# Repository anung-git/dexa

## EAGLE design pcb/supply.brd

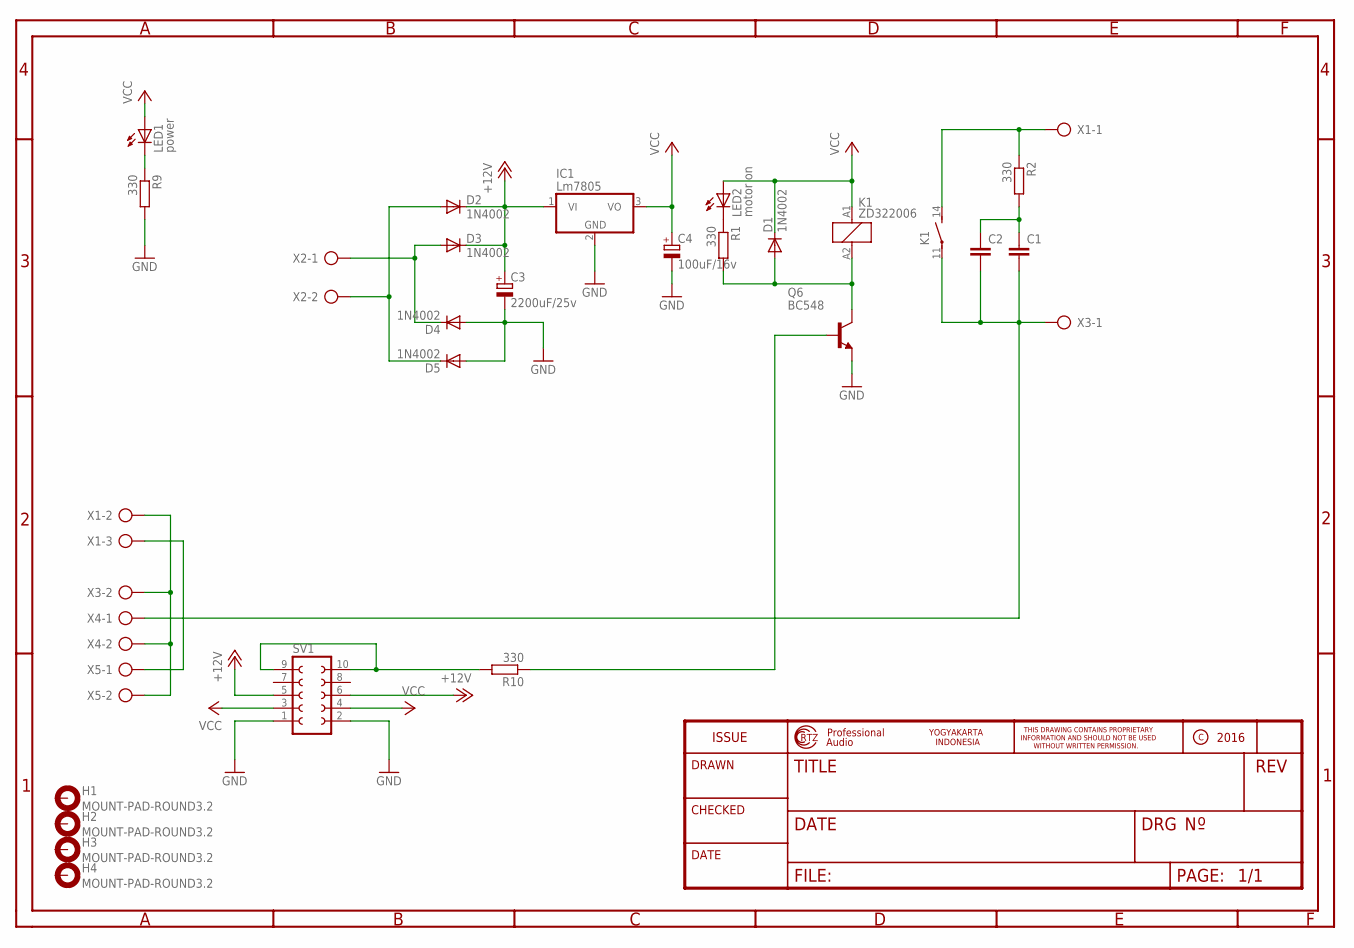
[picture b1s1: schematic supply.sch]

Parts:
C1: C-EU150-084X183; C150-084X183
C2: C-EU102-043X133; C102-043X133
C3: 2200uF/25v; E5-8,5
C4: 100uF/16v; B45181B
D1, D2, D3, D4, D5: 1N4002; DO35-10
H1, H2, H3, H4: MOUNT-PAD-ROUND3.2; 3,2-PAD
IC1: Lm7805; TO220V
K1: ZD322006; ZD2
LED1: power; LED5MM
LED2: motor on; LED5MM
Q6: BC548; TO92-EBC
R1, R2, R9, R10: 330; 0207/7
SV1: FE05-2
X1: AK500/3
X2, X3, X4, X5: AK500/2

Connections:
+12V: C3.+, D2.C, D3.C, IC1.1 (VI), SV1.5, SV1.6
GND: C3.-, C4.-, D4.A, D5.A, IC1.2 (GND), Q6.E, R9.2, SV1.1, SV1.2
GND1: D1.A, K1.A2 (2), Q6.C, R1.2
unnamed: LED2.K (C), R1.1
unnamed: LED1.K (C), R9.1
unnamed: D3.A, D4.C, X2.1
unnamed: D2.A, D5.C, X2.2
unnamed: C1.1, C2.1, R2.2
unnamed: C1.2, C2.2, K1.11, X3.1, X4.1
unnamed: K1.14 (S), R2.1, X1.1
unnamed: X1.2, X3.2, X4.2, X5.2
unnamed: X1.3, X5.1
unnamed: R10.2, SV1.9, SV1.10
unnamed: Q6.B, R10.1
VCC: C4.+, D1.C, IC1.3 (VO), K1.A1 (1), LED1.A, LED2.A, SV1.3, SV1.4

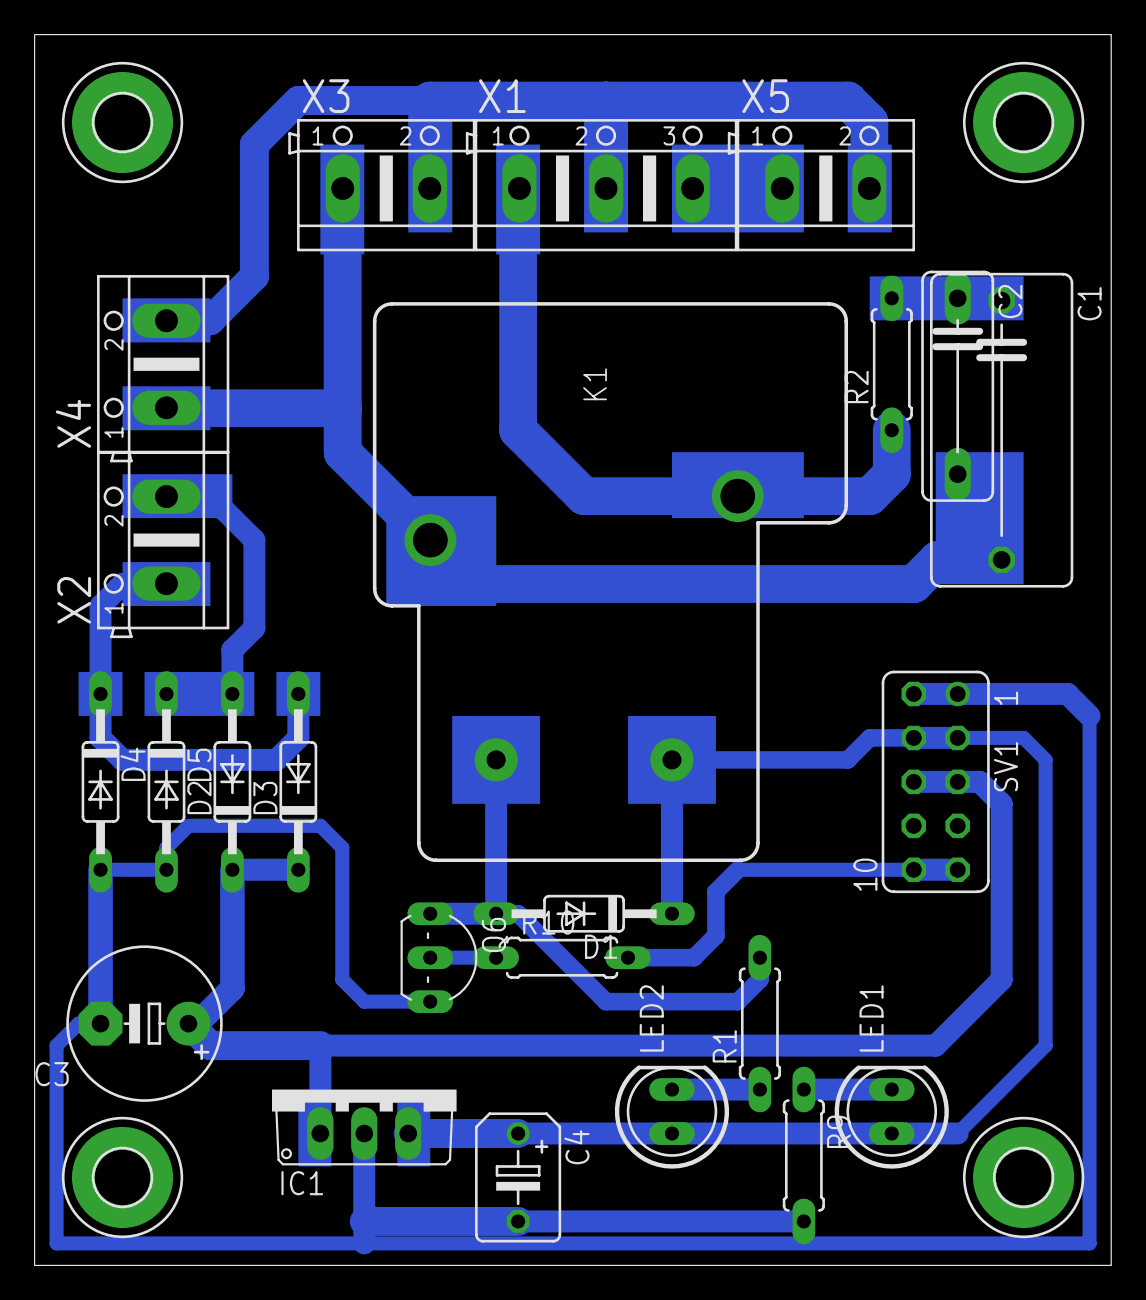
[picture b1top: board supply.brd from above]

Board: 2 copper layers, 62.2 x 71.1 mm, 28 parts (0 on the bottom side), 15 nets.

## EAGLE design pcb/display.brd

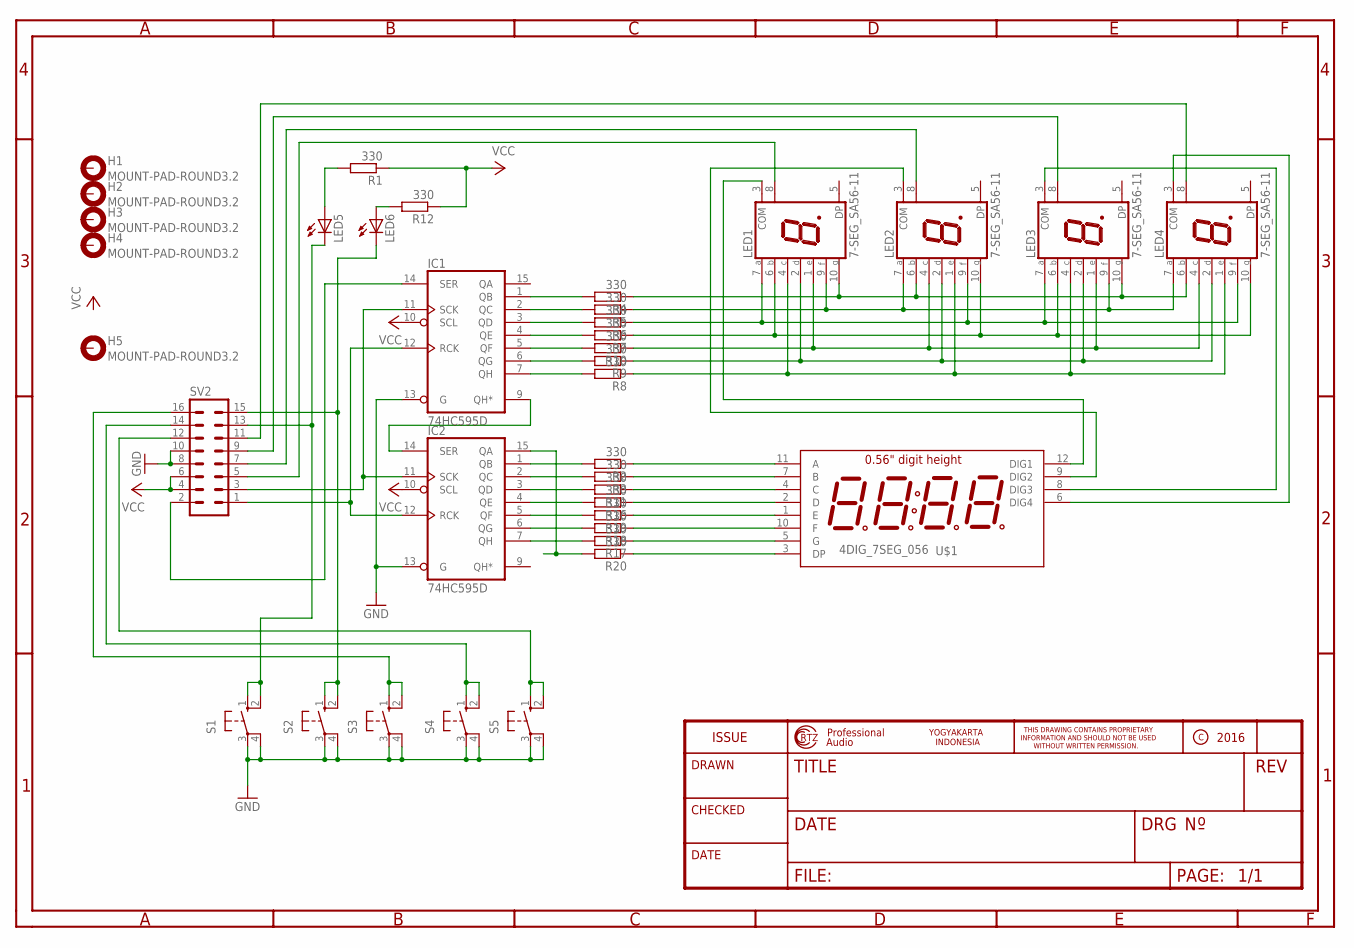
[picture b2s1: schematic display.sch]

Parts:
H1, H2, H3, H4, H5: MOUNT-PAD-ROUND3.2; 3,2-PAD
IC1, IC2: 74HC595D; SO16
LED1, LED2, LED3, LED4: 7-SEG_SA56-11; SA56-11
LED5, LED6: LED5MM
R1, R2, R3, R4, R5, R6, R7, R8, R9, R10, R11, R12, R16, R17, R18, R19, R20: 330; 0207/7
S1, S2, S3, S4, S5: 40-XX; B3F-40XX
SV2: MA08-2W
U$1: 4DIG_7SEG_056

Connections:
GND: IC1.8 (GND), IC1.13 (G), IC2.8 (GND), IC2.13 (G), S1.3, S1.4 (P1), S2.3, S2.4 (P1), S3.3, S3.4 (P1), S4.3, S4.4 (P1), S5.3, S5.4 (P1), SV2.8, SV2.10
unnamed: IC1.2 (QC), R5.2
unnamed: LED1.7 (A), LED2.9 (F), LED3.7 (A), LED4.9 (F), R6.1
unnamed: LED1.1 (E), LED2.4 (C), LED3.1 (E), LED4.4 (C), R10.1
unnamed: LED1.2 (D), LED2.2 (D), LED3.2 (D), LED4.2 (D), R9.1
unnamed: LED1.6 (B), LED2.10 (G), LED3.6 (B), LED4.10 (G), R7.1
unnamed: LED1.3 (COM), U$1.12 (DIG1)
unnamed: LED2.3 (COM), U$1.9 (DIG2)
unnamed: LED1.4 (C), LED2.1 (E), LED3.4 (C), LED4.1 (E), R8.1
unnamed: IC2.2 (QC), R3.2
unnamed: IC2.3 (QD), R11.2
unnamed: IC1.11 (SCK), IC2.11 (SCK), SV2.3
unnamed: IC1.3 (QD), R6.2
unnamed: IC1.12 (RCK), IC2.12 (RCK), SV2.1
unnamed: LED3.3 (COM), U$1.8 (DIG3)
unnamed: LED4.3 (COM), U$1.6 (DIG4)
unnamed: IC1.4 (QE), R7.2
unnamed: IC1.5 (QF), R10.2
unnamed: IC1.6 (QG), R9.2
unnamed: IC1.7 (QH), R8.2
unnamed: IC1.1 (QB), R4.2
unnamed: IC1.14 (SER), SV2.2
unnamed: IC2.4 (QE), R16.2
unnamed: IC2.6 (QG), R18.2
unnamed: LED4.8 (COM), SV2.11
unnamed: LED2.8 (COM), SV2.7
unnamed: LED3.8 (COM), SV2.9
unnamed: LED1.10 (G), LED2.6 (B), LED3.10 (G), LED4.6 (B), R4.1
unnamed: LED1.8 (COM), SV2.5
unnamed: LED5.A, R1.2
unnamed: LED6.A, R12.2
unnamed: IC2.5 (QF), R19.2
unnamed: LED1.9 (F), LED2.7 (A), LED3.9 (F), LED4.7 (A), R5.1
unnamed: IC2.7 (QH), R17.2
unnamed: IC2.1 (QB), R2.2
unnamed: R2.1, U$1.11 (A)
unnamed: R3.1, U$1.7 (B)
unnamed: R11.1, U$1.4 (C)
unnamed: R16.1, U$1.2 (D)
unnamed: R17.1, U$1.5 (G)
unnamed: R18.1, U$1.10 (F)
unnamed: R19.1, U$1.1 (E)
unnamed: R20.1, U$1.3 (DP)
unnamed: IC2.15 (QA), R20.2
unnamed: LED5.K (C), S1.1 (S), S1.2 (S1), SV2.13
unnamed: LED6.K (C), S2.1 (S), S2.2 (S1), SV2.15
unnamed: S3.1 (S), S3.2 (S1), SV2.16
unnamed: S4.1 (S), S4.2 (S1), SV2.14
unnamed: S5.1 (S), S5.2 (S1), SV2.12
unnamed: IC1.9 (QH*), IC2.14 (SER)
VCC: IC1.10 (SCL), IC1.16 (VCC), IC2.10 (SCL), IC2.16 (VCC), R1.1, R12.1, SV2.4, SV2.6

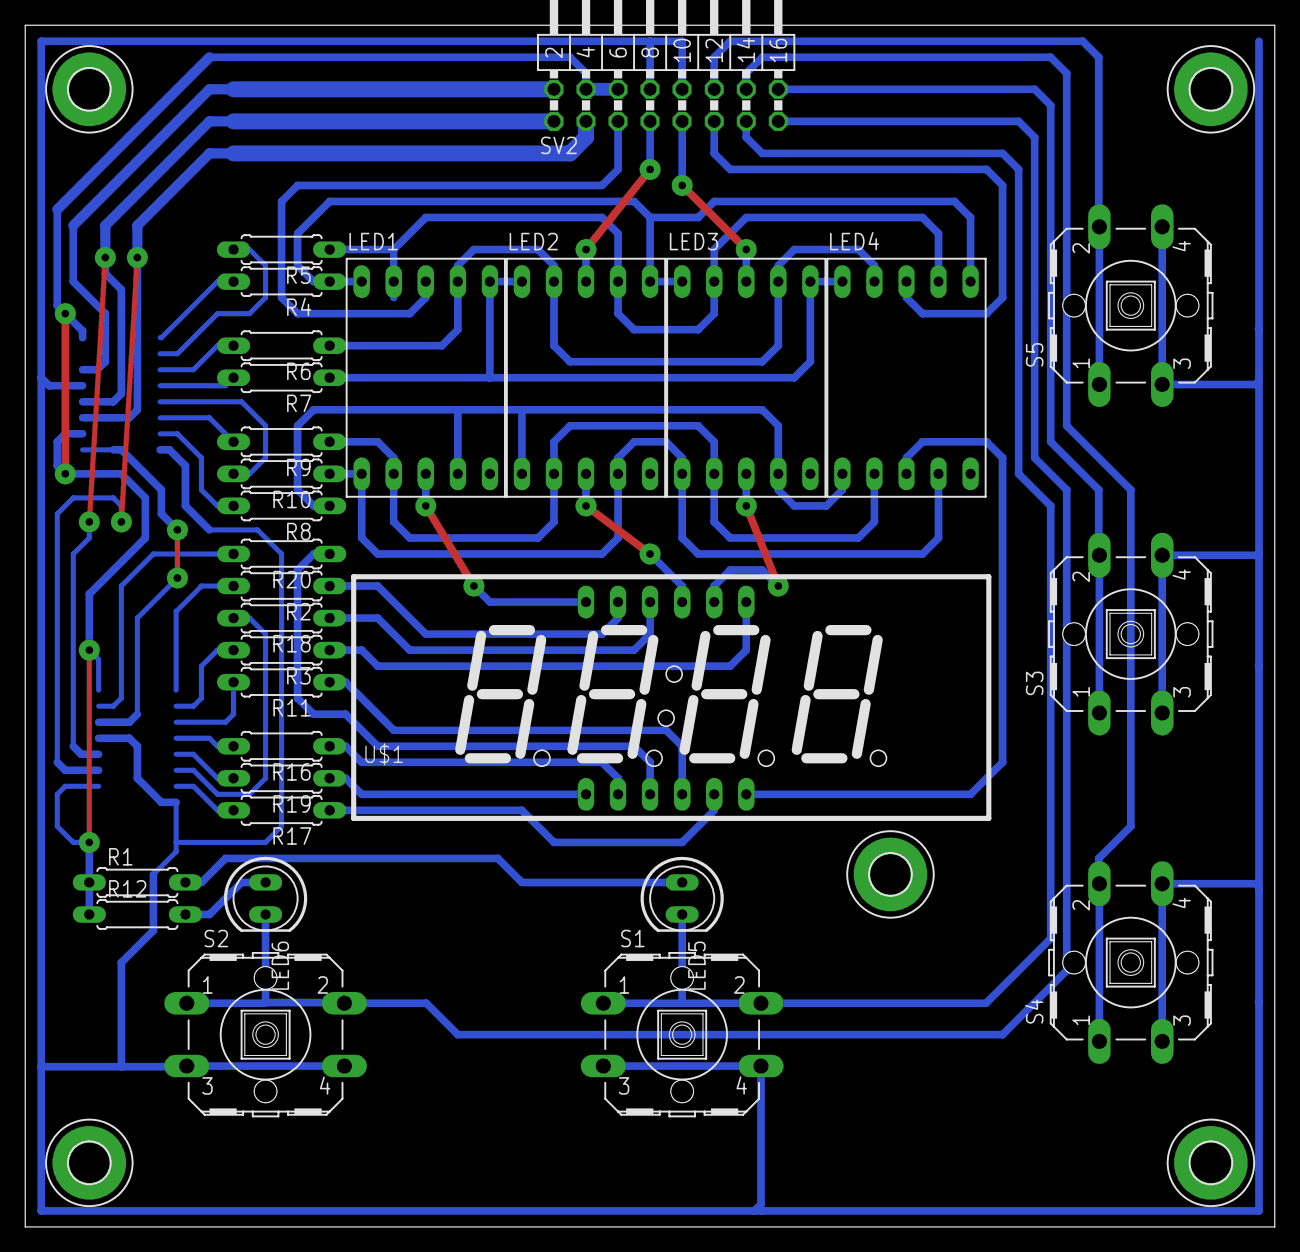
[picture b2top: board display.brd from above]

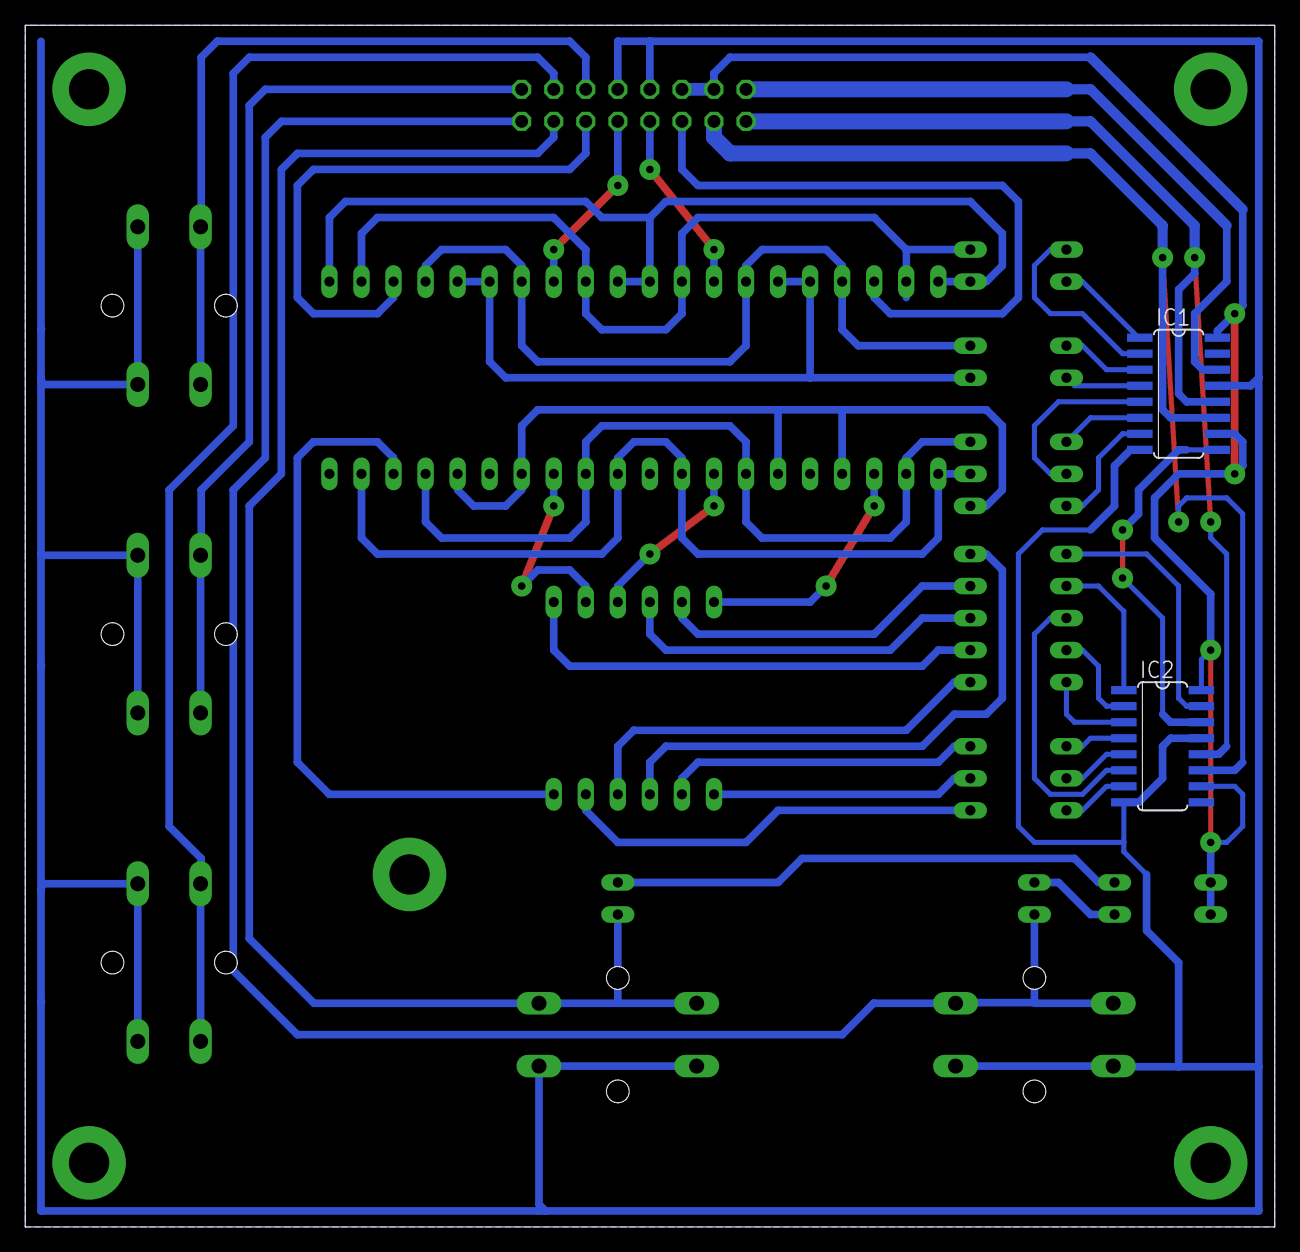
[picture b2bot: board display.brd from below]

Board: 2 copper layers, 99.0 x 95.2 mm, 37 parts (2 on the bottom side), 51 nets.

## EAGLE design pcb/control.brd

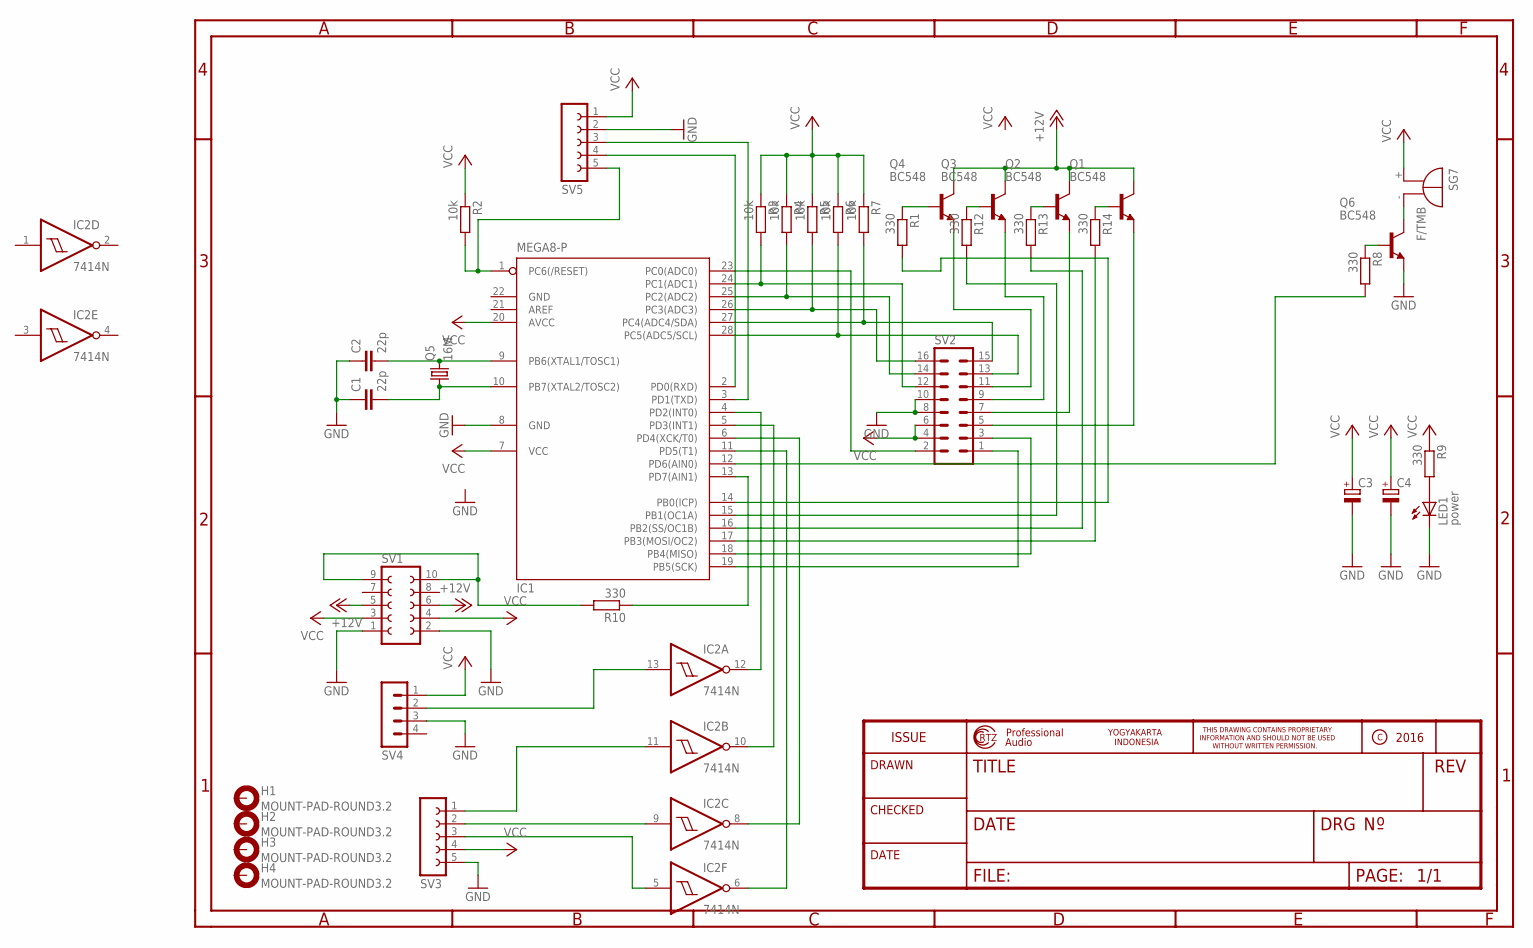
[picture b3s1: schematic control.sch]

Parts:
C1, C2: 22p; C025-025X050
C3, C4: CPOL-EUB45181B; B45181B
H1, H2, H3, H4: MOUNT-PAD-ROUND3.2; 3,2-PAD
IC1: MEGA8-P; DIL28-3
IC2: 7414N; DIL14
LED1: power; LED5MM
Q1, Q2, Q3, Q4, Q6: BC548; TO92-EBC
Q5: 16M; HC49U-V
R1, R8, R9, R10, R12, R13, R14: 330; 0207/7
R2, R3, R4, R5, R6, R7: 10k; 0207/7
SG7: F/TMB
SV1: FE05-2
SV2: MA08-2
SV3, SV5: FE05-1
SV4: MA04-1

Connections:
+12V: Q1.C, Q2.C, Q3.C, Q4.C, SV1.5, SV1.6
GND: C1.1, C2.1, C3.-, C4.-, IC1.8 (GND), IC1.22 (GND), IC2.7 (GND), LED1.K (C), Q6.E, SV1.1, SV1.2, SV2.8, SV2.10, SV3.5, SV4.3, SV5.2
unnamed: IC1.1 (PC6(/RESET)), R2.2, SV5.5
unnamed: C1.2, IC1.10 (PB7(XTAL2/TOSC2)), Q5.1
unnamed: C2.2, IC1.9 (PB6(XTAL1/TOSC1)), Q5.2
unnamed: IC1.24 (PC1(ADC1)), R3.2, SV2.12
unnamed: IC1.23 (PC0(ADC0)), SV2.2
unnamed: IC1.15 (PB1(OC1A)), R12.2
unnamed: IC1.16 (PB2(SS/OC1B)), R13.2
unnamed: IC1.17 (PB3(MOSI/OC2)), R14.2
unnamed: IC1.28 (PC5(ADC5/SCL)), R6.2, SV2.13
unnamed: Q4.B, R1.1
unnamed: Q6.C, SG7.-
unnamed: Q6.B, R8.1
unnamed: LED1.A, R9.2
unnamed: R10.2, SV1.9, SV1.10
unnamed: IC1.4 (PD2(INT0)), IC2.12 (O)
unnamed: IC1.13 (PD7(AIN1)), R10.1
unnamed: IC1.5 (PD3(INT1)), IC2.10 (O)
unnamed: Q3.B, R12.1
unnamed: IC1.6 (PD4(XCK/T0)), IC2.8 (O)
unnamed: IC1.12 (PD6(AIN0)), R8.2
unnamed: Q4.E, SV2.11
unnamed: Q2.E, SV2.7
unnamed: Q3.E, SV2.9
unnamed: IC2.13 (I), SV4.2
unnamed: Q1.E, SV2.5
unnamed: Q2.B, R13.1
unnamed: Q1.B, R14.1
unnamed: IC2.11 (I), SV3.1
unnamed: IC2.9 (I), SV3.2
unnamed: IC2.5 (I), SV3.3
unnamed: IC1.11 (PD5(T1)), IC2.6 (O)
unnamed: IC1.27 (PC4(ADC4/SDA)), R7.2, SV2.15
unnamed: IC1.2 (PD0(RXD)), SV5.4
unnamed: IC1.3 (PD1(TXD)), SV5.3
unnamed: IC1.14 (PB0(ICP)), R1.2
unnamed: IC1.19 (PB5(SCK)), SV2.1
unnamed: IC1.18 (PB4(MISO)), SV2.3
unnamed: IC1.25 (PC2(ADC2)), R4.2, SV2.14
unnamed: IC1.26 (PC3(ADC3)), R5.2, SV2.16
VCC: C3.+, C4.+, IC1.7 (VCC), IC1.20 (AVCC), IC2.14 (VCC), R2.1, R3.1, R4.1, R5.1, R6.1, R7.1, R9.1, SG7.+, SV1.3, SV1.4, SV2.4, SV2.6, SV3.4, SV4.1, SV5.1

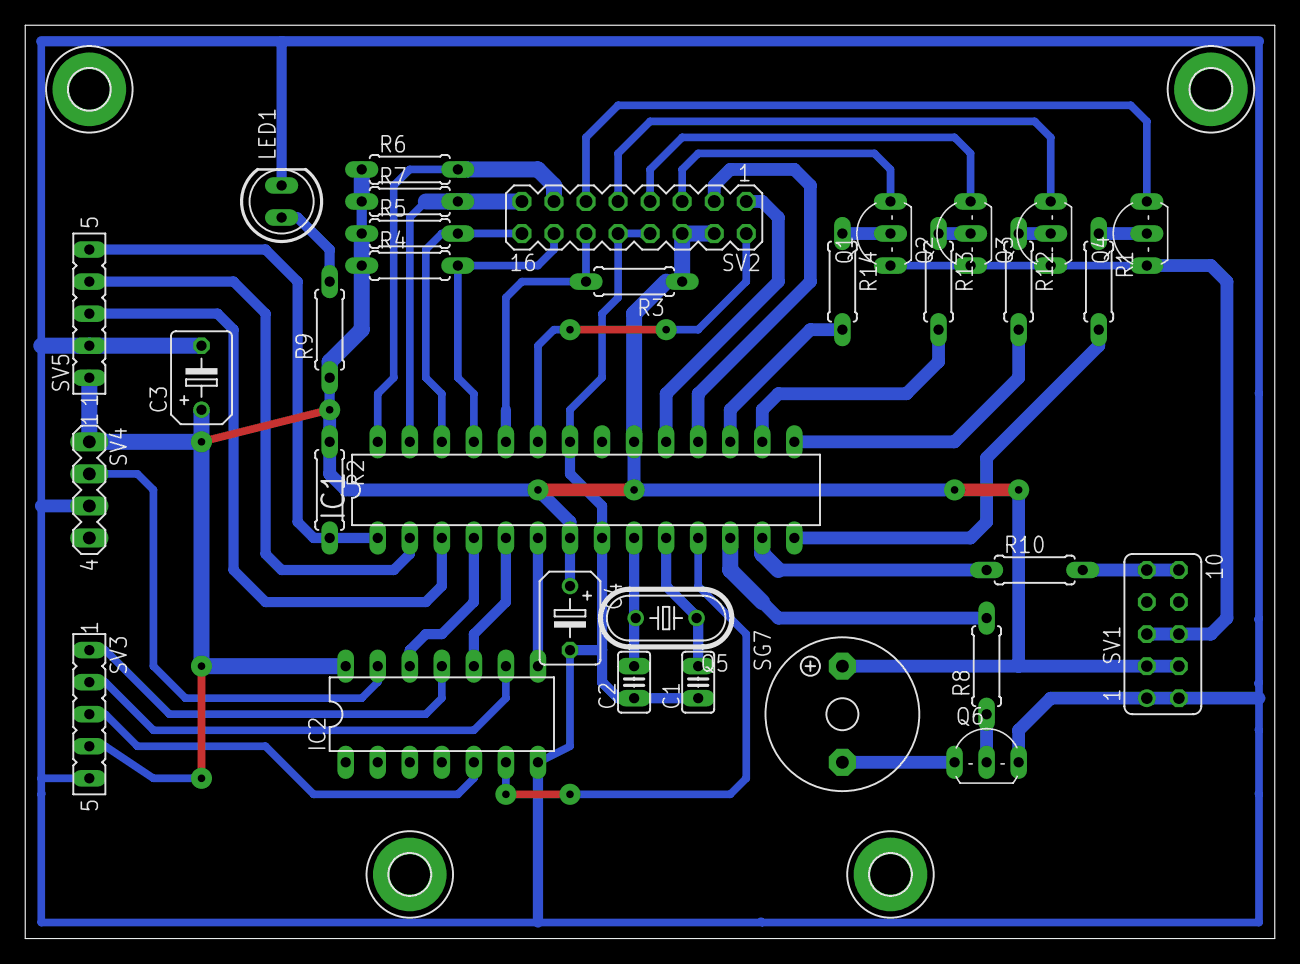
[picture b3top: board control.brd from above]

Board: 2 copper layers, 99.0 x 72.4 mm, 36 parts (0 on the bottom side), 42 nets.

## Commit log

2021-08-27 upload
2021-08-27 interup rpm
2021-08-28 add rpm display
2021-08-29 add class buzer
2021-08-29 disable button
2021-08-29 edit pcb
2021-08-29 ganti pcb
2021-08-30 auto reset
2021-08-30 pin tombol
2021-09-05 disc encoder

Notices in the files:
parts and their libraries:
dframes - Copy: Copyright (C) 2004, Bob Starr (bobstarr@mindspring.com)
